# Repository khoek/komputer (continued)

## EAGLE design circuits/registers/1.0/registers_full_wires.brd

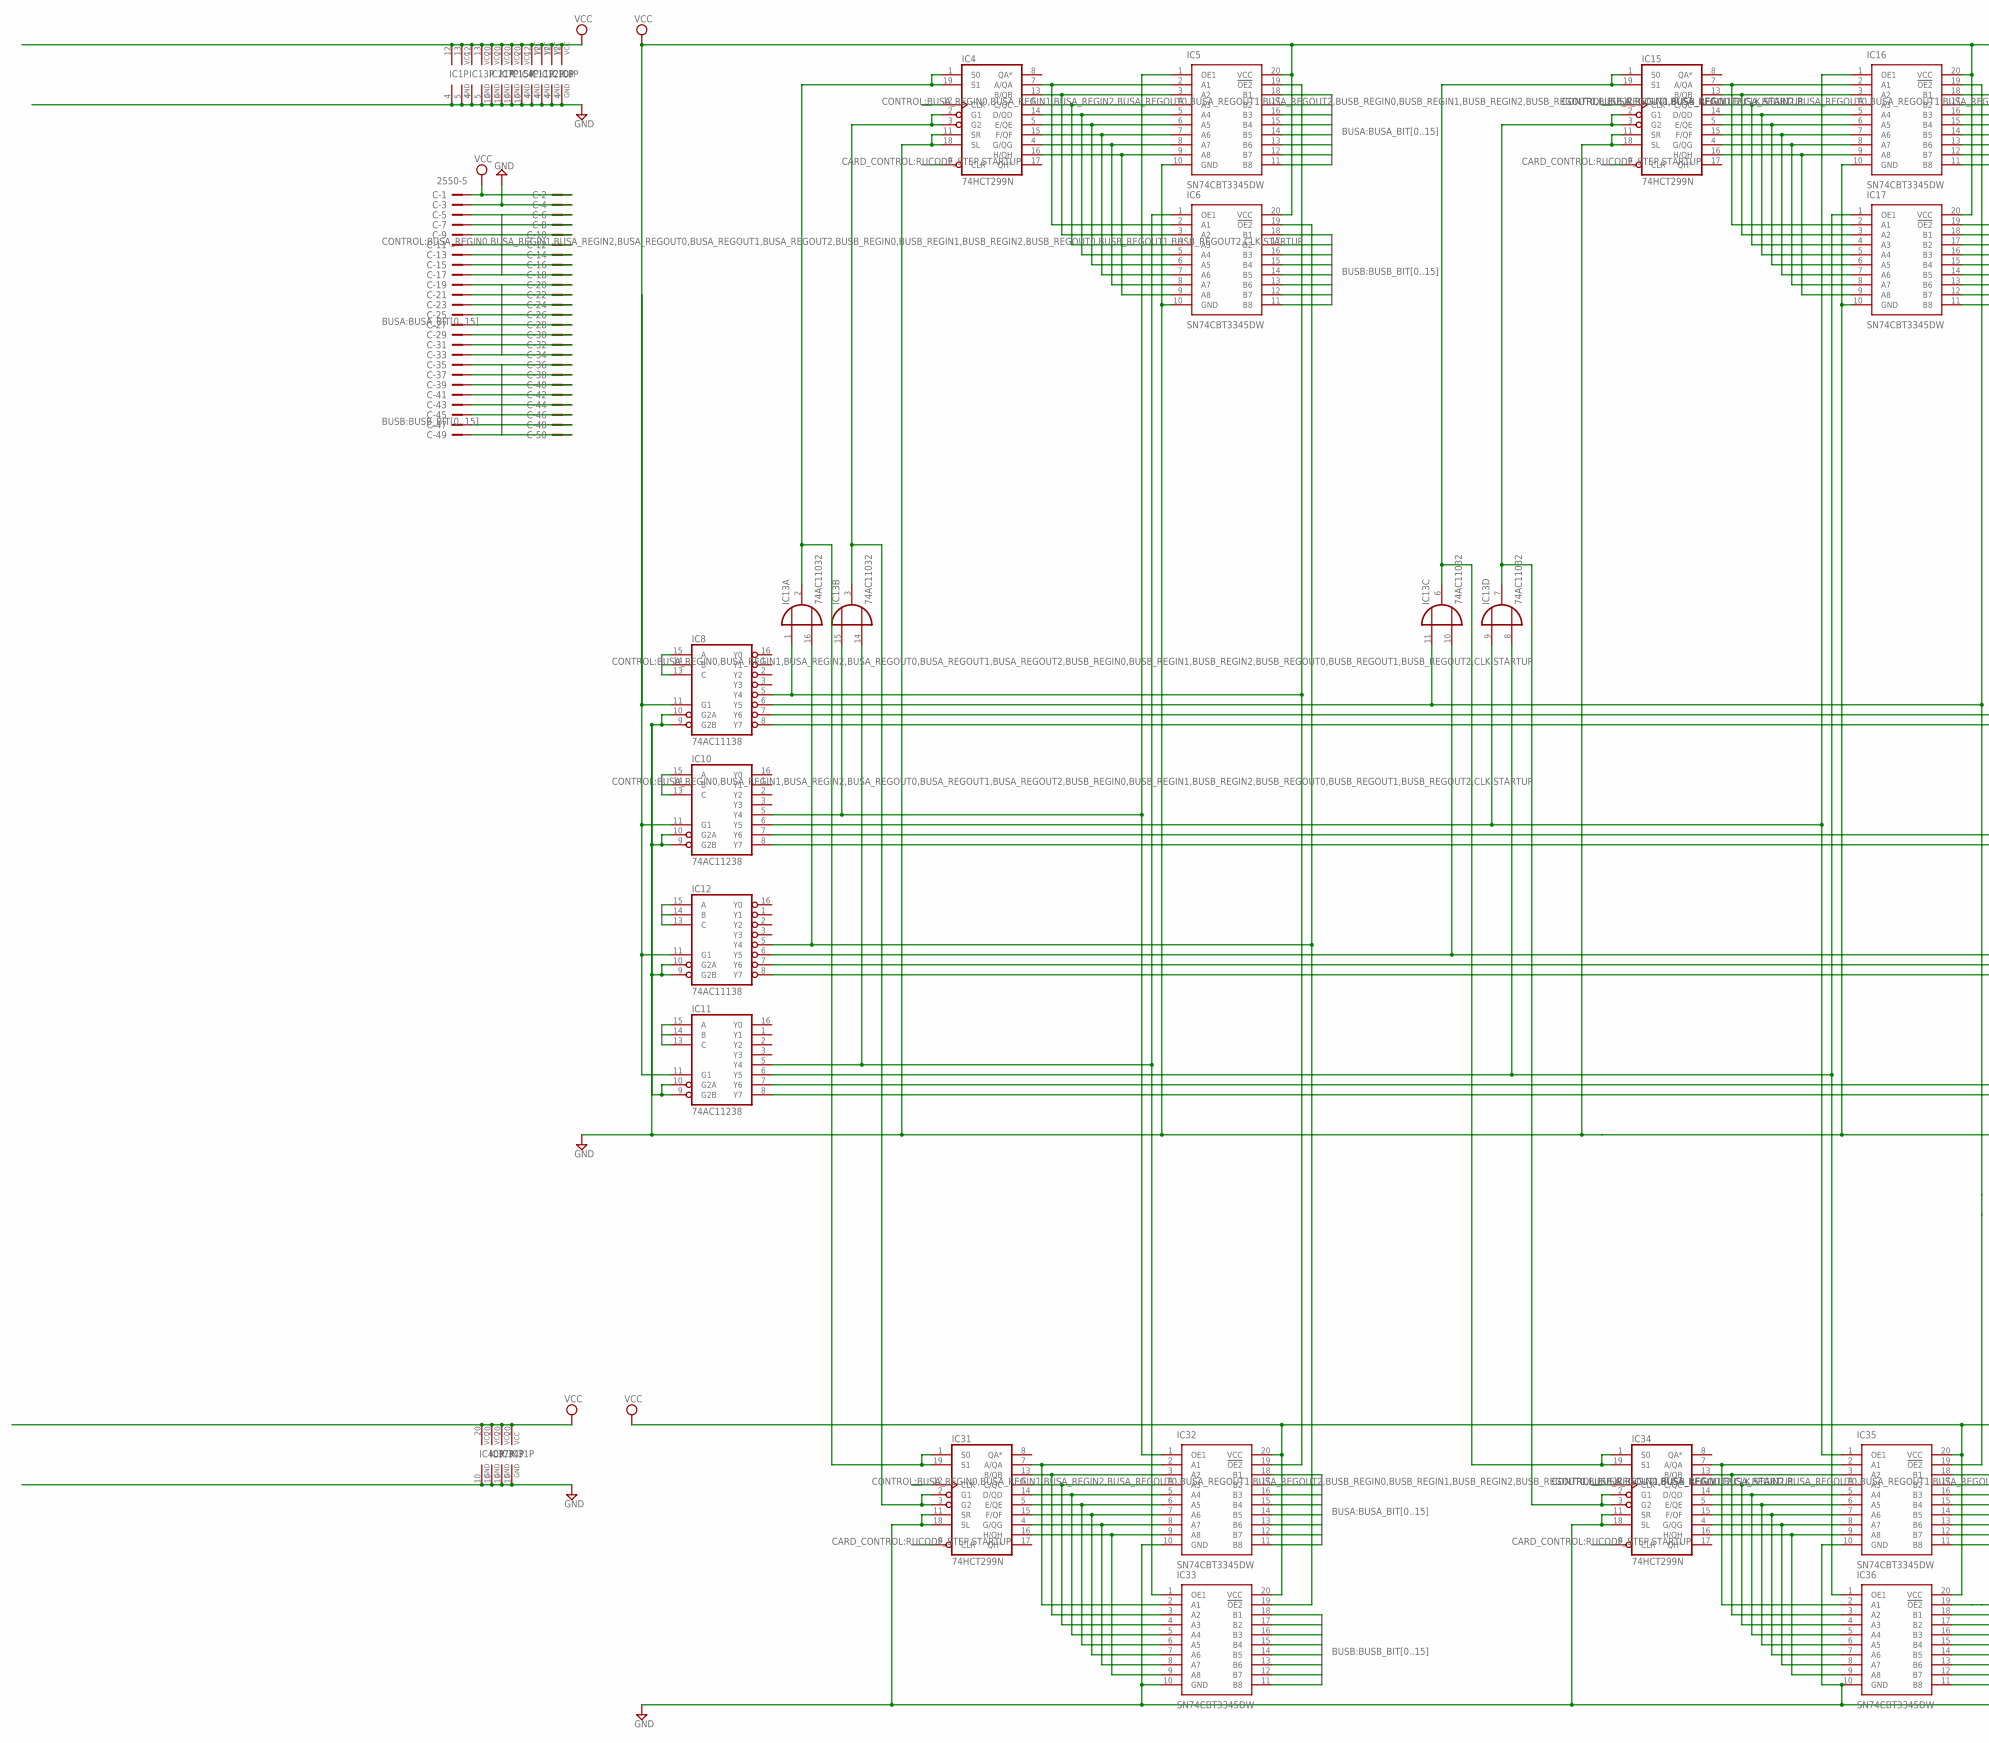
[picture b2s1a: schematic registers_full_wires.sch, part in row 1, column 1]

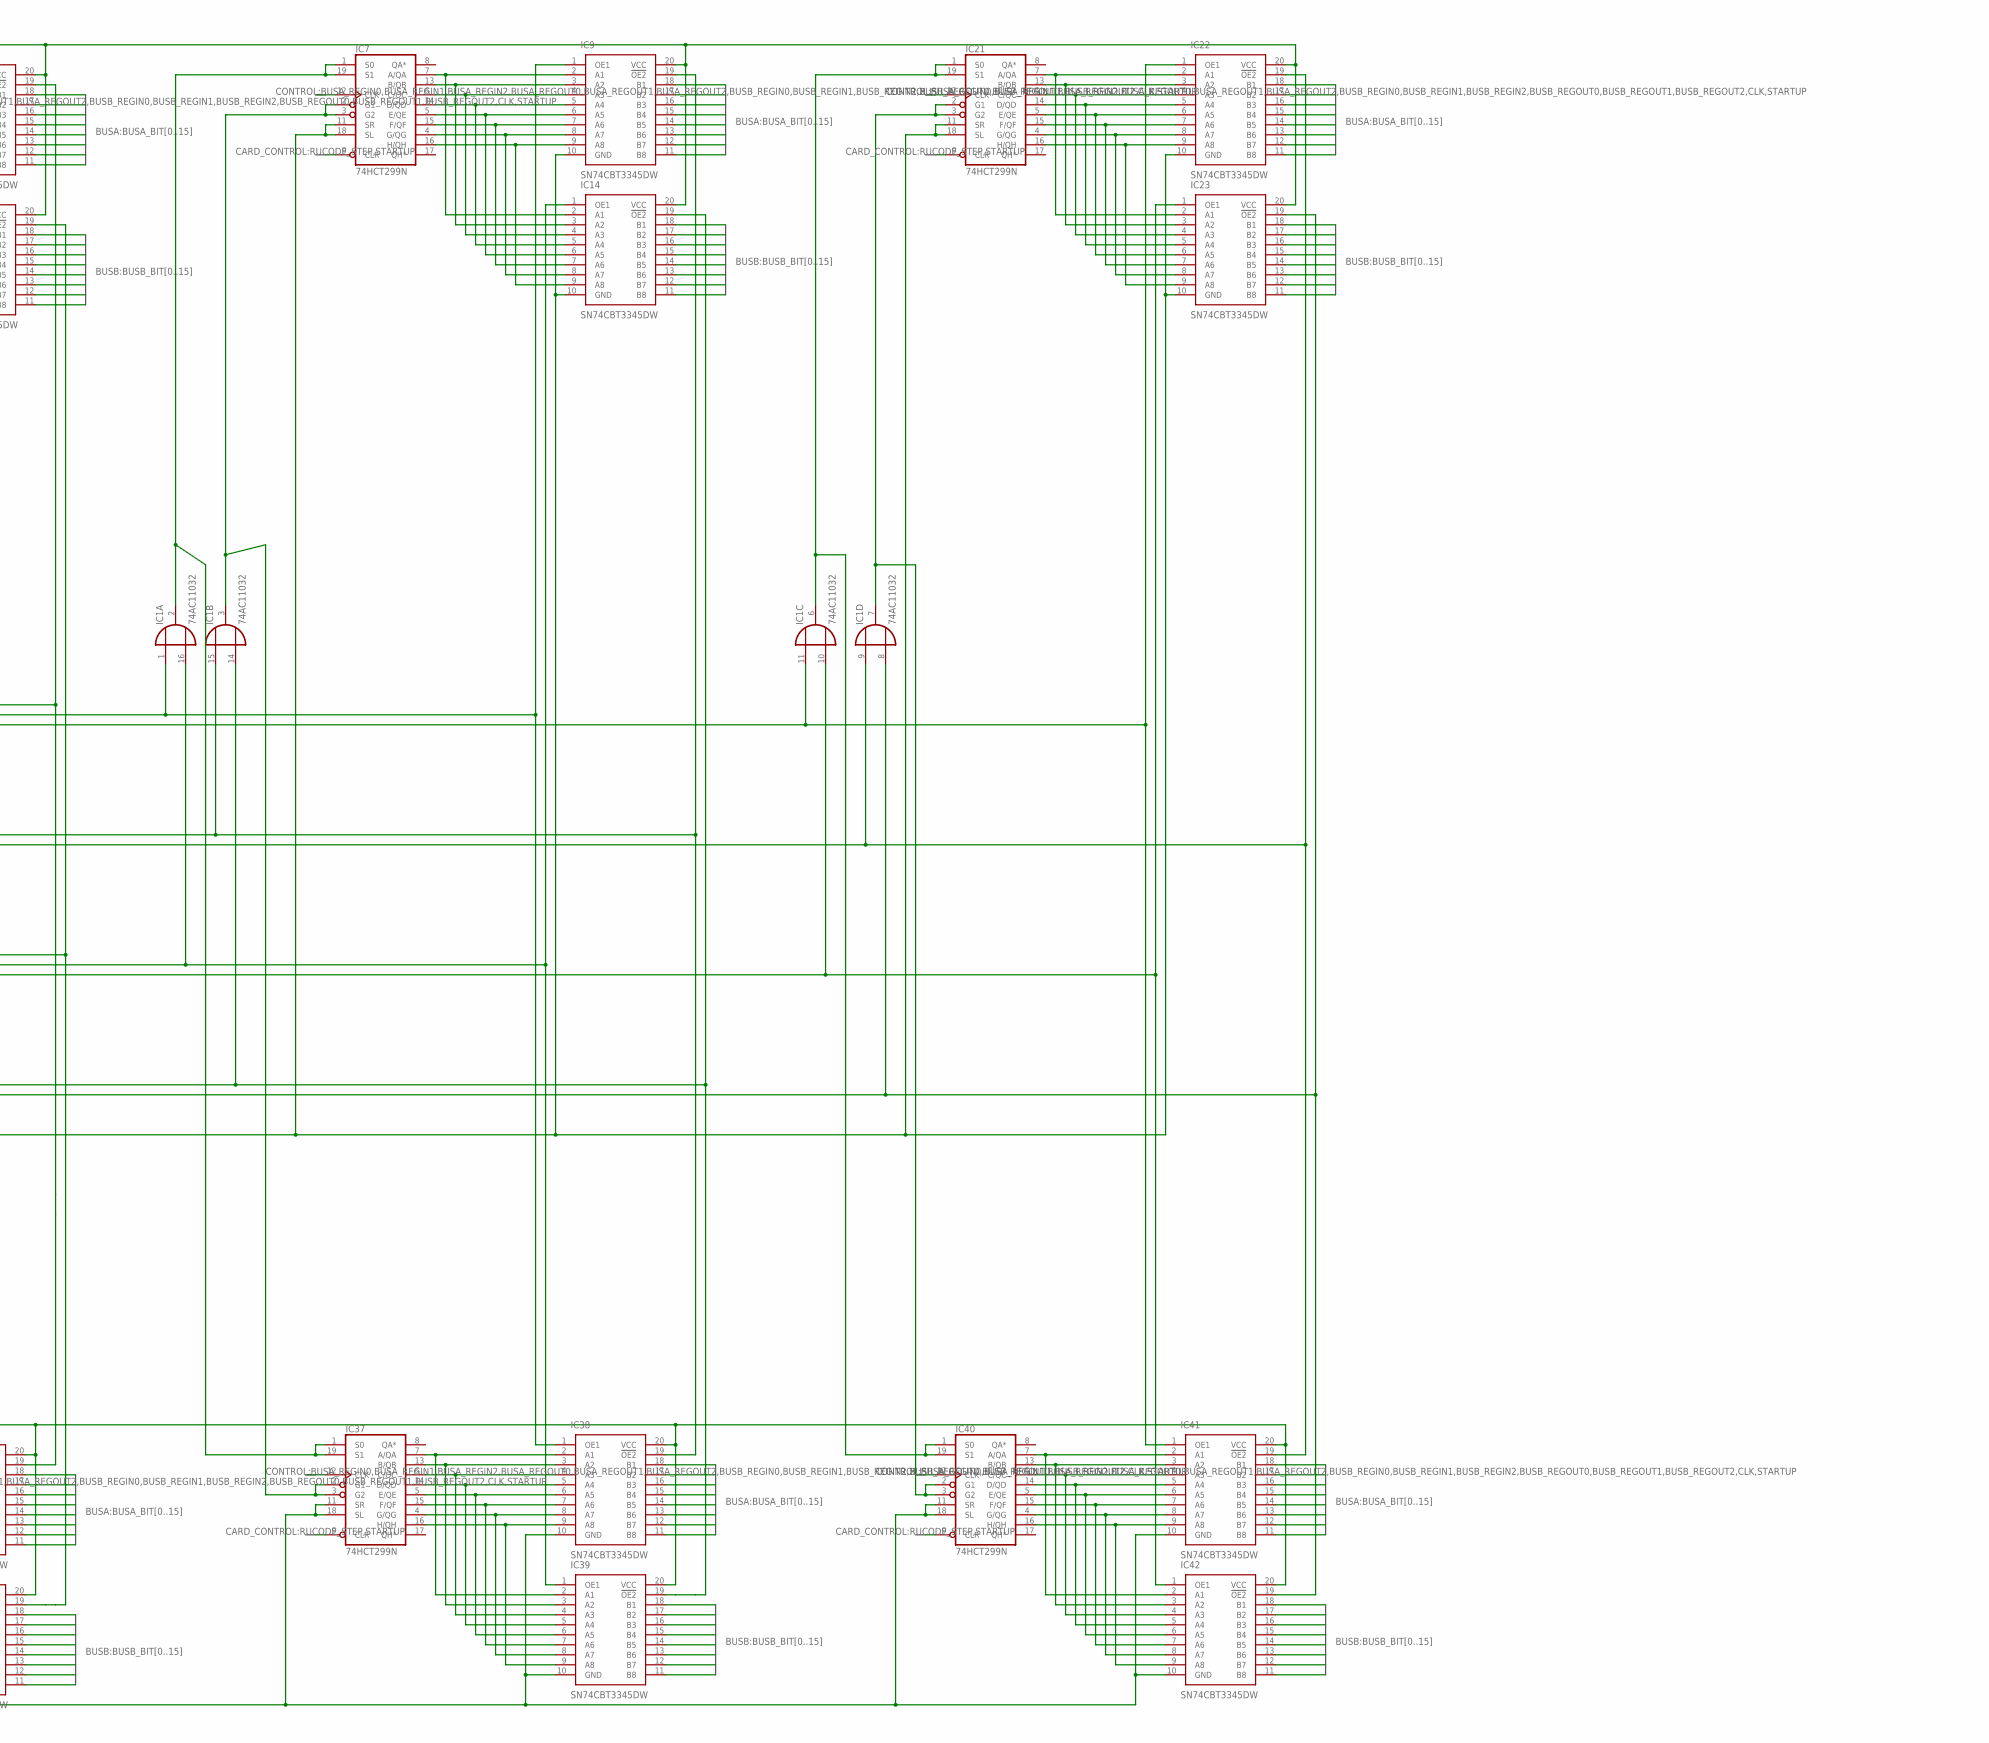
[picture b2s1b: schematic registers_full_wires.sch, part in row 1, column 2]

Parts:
C: 2550-5; PAK100/2500-5-50
IC1, IC13: 74AC11032; DIL16
IC4, IC7, IC15, IC21, IC31, IC34, IC37, IC40: 74HCT299N; DIL20
IC5, IC6, IC9, IC14, IC16, IC17, IC22, IC23, IC32, IC33, IC35, IC36, IC38, IC39, IC41, IC42: SN74CBT3345DW; SOIC127P1030X265-20N
IC8, IC12: 74AC11138; DIL16
IC10, IC11: 74AC11238; DIL16

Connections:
BUSA_BIT0: C.19, IC5.18 (B1), IC9.18 (B1), IC16.18 (B1), IC22.18 (B1)
BUSA_BIT1: C.20, IC5.17 (B2), IC9.17 (B2), IC16.17 (B2), IC22.17 (B2)
BUSA_BIT2: C.21, IC5.16 (B3), IC9.16 (B3), IC16.16 (B3), IC22.16 (B3)
BUSA_BIT3: C.22, IC5.15 (B4), IC9.15 (B4), IC16.15 (B4), IC22.15 (B4)
BUSA_BIT4: C.23, IC5.14 (B5), IC9.14 (B5), IC16.14 (B5), IC22.14 (B5)
BUSA_BIT5: C.24, IC5.13 (B6), IC9.13 (B6), IC16.13 (B6), IC22.13 (B6)
BUSA_BIT6: C.25, IC5.12 (B7), IC9.12 (B7), IC16.12 (B7), IC22.12 (B7)
BUSA_BIT7: C.26, IC5.11 (B8), IC9.11 (B8), IC16.11 (B8), IC22.11 (B8)
BUSA_BIT8: C.27, IC32.18 (B1), IC35.18 (B1), IC38.18 (B1), IC41.18 (B1)
BUSA_BIT9: C.28, IC32.17 (B2), IC35.17 (B2), IC38.17 (B2), IC41.17 (B2)
BUSA_BIT10: C.29, IC32.16 (B3), IC35.16 (B3), IC38.16 (B3), IC41.16 (B3)
BUSA_BIT11: C.30, IC32.15 (B4), IC35.15 (B4), IC38.15 (B4), IC41.15 (B4)
BUSA_BIT12: C.31, IC32.14 (B5), IC35.14 (B5), IC38.14 (B5), IC41.14 (B5)
BUSA_BIT13: C.32, IC32.13 (B6), IC35.13 (B6), IC38.13 (B6), IC41.13 (B6)
BUSA_BIT14: C.33, IC32.12 (B7), IC35.12 (B7), IC38.12 (B7), IC41.12 (B7)
BUSA_BIT15: C.34, IC32.11 (B8), IC35.11 (B8), IC38.11 (B8), IC41.11 (B8)
BUSA_REGIN0: C.7, IC8.15 (A)
BUSA_REGIN1: C.9, IC8.14 (B)
BUSA_REGIN2: C.11, IC8.13 (C)
BUSA_REGOUT0: C.13, IC10.15 (A)
BUSA_REGOUT1: C.15, IC10.14 (B)
BUSA_REGOUT2: C.17, IC10.13 (C)
BUSB_BIT0: C.35, IC6.18 (B1), IC14.18 (B1), IC17.18 (B1), IC23.18 (B1)
BUSB_BIT1: C.36, IC6.17 (B2), IC14.17 (B2), IC17.17 (B2), IC23.17 (B2)
BUSB_BIT2: C.37, IC6.16 (B3), IC14.16 (B3), IC17.16 (B3), IC23.16 (B3)
BUSB_BIT3: C.38, IC6.15 (B4), IC14.15 (B4), IC17.15 (B4), IC23.15 (B4)
BUSB_BIT4: C.39, IC6.14 (B5), IC14.14 (B5), IC17.14 (B5), IC23.14 (B5)
BUSB_BIT5: C.40, IC6.13 (B6), IC14.13 (B6), IC17.13 (B6), IC23.13 (B6)
BUSB_BIT6: C.41, IC6.12 (B7), IC14.12 (B7), IC17.12 (B7), IC23.12 (B7)
BUSB_BIT7: C.42, IC6.11 (B8), IC14.11 (B8), IC17.11 (B8), IC23.11 (B8)
BUSB_BIT8: C.43, IC33.18 (B1), IC36.18 (B1), IC39.18 (B1), IC42.18 (B1)
BUSB_BIT9: C.44, IC33.17 (B2), IC36.17 (B2), IC39.17 (B2), IC42.17 (B2)
BUSB_BIT10: C.45, IC33.16 (B3), IC36.16 (B3), IC39.16 (B3), IC42.16 (B3)
BUSB_BIT11: C.46, IC33.15 (B4), IC36.15 (B4), IC39.15 (B4), IC42.15 (B4)
BUSB_BIT12: C.47, IC33.14 (B5), IC36.14 (B5), IC39.14 (B5), IC42.14 (B5)
BUSB_BIT13: C.48, IC33.13 (B6), IC36.13 (B6), IC39.13 (B6), IC42.13 (B6)
BUSB_BIT14: C.49, IC33.12 (B7), IC36.12 (B7), IC39.12 (B7), IC42.12 (B7)
BUSB_BIT15: C.50, IC33.11 (B8), IC36.11 (B8), IC39.11 (B8), IC42.11 (B8)
BUSB_REGIN0: C.8, IC12.15 (A)
BUSB_REGIN1: C.10, IC12.14 (B)
BUSB_REGIN2: C.12, IC12.13 (C)
BUSB_REGOUT0: C.14, IC11.15 (A)
BUSB_REGOUT1: C.16, IC11.14 (B)
BUSB_REGOUT2: C.18, IC11.13 (C)
CLK: C.5, IC4.12 (CLK), IC7.12 (CLK), IC15.12 (CLK), IC21.12 (CLK), IC31.12 (CLK), IC34.12 (CLK), IC37.12 (CLK), IC40.12 (CLK)
GND: C.3, C.4, IC1.4 (GND), IC1.5 (GND), IC4.10 (GND), IC4.11 (SR), IC4.18 (SL), IC5.10 (GND), IC6.10 (GND), IC7.10 (GND), IC7.11 (SR), IC7.18 (SL), IC8.4 (GND), IC8.9 (G2B), IC8.10 (G2A), IC9.10 (GND), IC10.4 (GND), IC10.9 (G2B), IC10.10 (G2A), IC11.4 (GND), IC11.9 (G2B), IC11.10 (G2A), IC12.4 (GND), IC12.9 (G2B), IC12.10 (G2A), IC13.4 (GND), IC13.5 (GND), IC14.10 (GND), IC15.10 (GND), IC15.11 (SR), IC15.18 (SL), IC16.10 (GND), IC17.10 (GND), IC21.10 (GND), IC21.11 (SR), IC21.18 (SL), IC22.10 (GND), IC23.10 (GND), IC31.10 (GND), IC31.11 (SR), IC31.18 (SL), IC32.10 (GND), IC33.10 (GND), IC34.10 (GND), IC34.11 (SR), IC34.18 (SL), IC35.10 (GND), IC36.10 (GND), IC37.10 (GND), IC37.11 (SR), IC37.18 (SL), IC38.10 (GND), IC39.10 (GND), IC40.10 (GND), IC40.11 (SR), IC40.18 (SL), IC41.10 (GND), IC42.10 (GND)
unnamed: IC34.16 (H/QH), IC35.9 (A8), IC36.9 (A8)
unnamed: IC1.8 (I2), IC11.8 (Y7), IC23.19 (!OE2), IC42.19 (!OE2)
unnamed: IC4.7 (A/QA), IC5.2 (A1), IC6.2 (A1)
unnamed: IC4.13 (B/QB), IC5.3 (A2), IC6.3 (A2)
unnamed: IC4.6 (C/QC), IC5.4 (A3), IC6.4 (A3)
unnamed: IC4.14 (D/QD), IC5.5 (A4), IC6.5 (A4)
unnamed: IC4.5 (E/QE), IC5.6 (A5), IC6.6 (A5)
unnamed: IC4.15 (F/QF), IC5.7 (A6), IC6.7 (A6)
unnamed: IC4.4 (G/QG), IC5.8 (A7), IC6.8 (A7)
unnamed: IC4.16 (H/QH), IC5.9 (A8), IC6.9 (A8)
unnamed: IC7.7 (A/QA), IC9.2 (A1), IC14.2 (A1)
unnamed: IC7.13 (B/QB), IC9.3 (A2), IC14.3 (A2)
unnamed: IC7.6 (C/QC), IC9.4 (A3), IC14.4 (A3)
unnamed: IC7.14 (D/QD), IC9.5 (A4), IC14.5 (A4)
unnamed: IC7.5 (E/QE), IC9.6 (A5), IC14.6 (A5)
unnamed: IC5.1 (OE1), IC10.5 (Y4), IC13.15 (I1), IC32.1 (OE1)
unnamed: IC7.15 (F/QF), IC9.7 (A6), IC14.7 (A6)
unnamed: IC7.4 (G/QG), IC9.8 (A7), IC14.8 (A7)
unnamed: IC7.16 (H/QH), IC9.9 (A8), IC14.9 (A8)
unnamed: IC15.7 (A/QA), IC16.2 (A1), IC17.2 (A1)
unnamed: IC15.13 (B/QB), IC16.3 (A2), IC17.3 (A2)
unnamed: IC15.6 (C/QC), IC16.4 (A3), IC17.4 (A3)
unnamed: IC15.14 (D/QD), IC16.5 (A4), IC17.5 (A4)
unnamed: IC15.5 (E/QE), IC16.6 (A5), IC17.6 (A5)
unnamed: IC15.15 (F/QF), IC16.7 (A6), IC17.7 (A6)
unnamed: IC15.4 (G/QG), IC16.8 (A7), IC17.8 (A7)
unnamed: IC15.16 (H/QH), IC16.9 (A8), IC17.9 (A8)
unnamed: IC21.7 (A/QA), IC22.2 (A1), IC23.2 (A1)
unnamed: IC21.13 (B/QB), IC22.3 (A2), IC23.3 (A2)
unnamed: IC21.6 (C/QC), IC22.4 (A3), IC23.4 (A3)
unnamed: IC21.14 (D/QD), IC22.5 (A4), IC23.5 (A4)
unnamed: IC21.5 (E/QE), IC22.6 (A5), IC23.6 (A5)
unnamed: IC21.15 (F/QF), IC22.7 (A6), IC23.7 (A6)
unnamed: IC21.4 (G/QG), IC22.8 (A7), IC23.8 (A7)
unnamed: IC21.16 (H/QH), IC22.9 (A8), IC23.9 (A8)
unnamed: IC5.19 (!OE2), IC8.5 (Y4), IC13.1 (I1), IC32.19 (!OE2)
unnamed: IC31.7 (A/QA), IC32.2 (A1), IC33.2 (A1)
unnamed: IC31.13 (B/QB), IC32.3 (A2), IC33.3 (A2)
unnamed: IC6.19 (!OE2), IC12.5 (Y4), IC13.16 (I2), IC33.19 (!OE2)
unnamed: IC31.6 (C/QC), IC32.4 (A3), IC33.4 (A3)
unnamed: IC31.14 (D/QD), IC32.5 (A4), IC33.5 (A4)
unnamed: IC4.2 (G1), IC4.3 (G2), IC13.3 (O), IC31.2 (G1), IC31.3 (G2)
unnamed: IC4.1 (S0), IC4.19 (S1), IC13.2 (O), IC31.1 (S0), IC31.19 (S1)
unnamed: IC31.5 (E/QE), IC32.6 (A5), IC33.6 (A5)
unnamed: IC31.15 (F/QF), IC32.7 (A6), IC33.7 (A6)
unnamed: IC31.4 (G/QG), IC32.8 (A7), IC33.8 (A7)
unnamed: IC31.16 (H/QH), IC32.9 (A8), IC33.9 (A8)
unnamed: IC34.7 (A/QA), IC35.2 (A1), IC36.2 (A1)
unnamed: IC34.13 (B/QB), IC35.3 (A2), IC36.3 (A2)
unnamed: IC34.6 (C/QC), IC35.4 (A3), IC36.4 (A3)
unnamed: IC34.14 (D/QD), IC35.5 (A4), IC36.5 (A4)
unnamed: IC13.7 (O), IC15.2 (G1), IC15.3 (G2), IC34.2 (G1), IC34.3 (G2)
unnamed: IC13.6 (O), IC15.1 (S0), IC15.19 (S1), IC34.1 (S0), IC34.19 (S1)
unnamed: IC34.5 (E/QE), IC35.6 (A5), IC36.6 (A5)
unnamed: IC34.15 (F/QF), IC35.7 (A6), IC36.7 (A6)
unnamed: IC34.4 (G/QG), IC35.8 (A7), IC36.8 (A7)
unnamed: IC37.7 (A/QA), IC38.2 (A1), IC39.2 (A1)
unnamed: IC37.13 (B/QB), IC38.3 (A2), IC39.3 (A2)
unnamed: IC37.6 (C/QC), IC38.4 (A3), IC39.4 (A3)
unnamed: IC37.14 (D/QD), IC38.5 (A4), IC39.5 (A4)
unnamed: IC1.3 (O), IC7.2 (G1), IC7.3 (G2), IC37.2 (G1), IC37.3 (G2)
unnamed: IC1.2 (O), IC7.1 (S0), IC7.19 (S1), IC37.1 (S0), IC37.19 (S1)
unnamed: IC37.5 (E/QE), IC38.6 (A5), IC39.6 (A5)
unnamed: IC37.15 (F/QF), IC38.7 (A6), IC39.7 (A6)
unnamed: IC37.4 (G/QG), IC38.8 (A7), IC39.8 (A7)
unnamed: IC37.16 (H/QH), IC38.9 (A8), IC39.9 (A8)
unnamed: IC40.7 (A/QA), IC41.2 (A1), IC42.2 (A1)
unnamed: IC40.13 (B/QB), IC41.3 (A2), IC42.3 (A2)
unnamed: IC40.6 (C/QC), IC41.4 (A3), IC42.4 (A3)
unnamed: IC40.14 (D/QD), IC41.5 (A4), IC42.5 (A4)
unnamed: IC1.7 (O), IC21.2 (G1), IC21.3 (G2), IC40.2 (G1), IC40.3 (G2)
unnamed: IC1.6 (O), IC21.1 (S0), IC21.19 (S1), IC40.1 (S0), IC40.19 (S1)
unnamed: IC40.5 (E/QE), IC41.6 (A5), IC42.6 (A5)
unnamed: IC40.15 (F/QF), IC41.7 (A6), IC42.7 (A6)
unnamed: IC40.4 (G/QG), IC41.8 (A7), IC42.8 (A7)
unnamed: IC40.16 (H/QH), IC41.9 (A8), IC42.9 (A8)
unnamed: IC6.1 (OE1), IC11.5 (Y4), IC13.14 (I2), IC33.1 (OE1)
unnamed: IC8.6 (Y5), IC13.11 (I1), IC16.19 (!OE2), IC35.19 (!OE2)
unnamed: IC12.6 (Y5), IC13.10 (I2), IC17.19 (!OE2), IC36.19 (!OE2)
unnamed: IC10.6 (Y5), IC13.9 (I1), IC16.1 (OE1), IC35.1 (OE1)
unnamed: IC11.6 (Y5), IC13.8 (I2), IC17.1 (OE1), IC36.1 (OE1)
unnamed: IC1.1 (I1), IC8.7 (Y6), IC9.1 (OE1), IC38.1 (OE1)
unnamed: IC1.16 (I2), IC12.7 (Y6), IC14.1 (OE1), IC39.1 (OE1)
unnamed: IC1.15 (I1), IC9.19 (!OE2), IC10.7 (Y6), IC38.19 (!OE2)
unnamed: IC1.14 (I2), IC11.7 (Y6), IC14.19 (!OE2), IC39.19 (!OE2)
unnamed: IC1.9 (I1), IC10.8 (Y7), IC22.19 (!OE2), IC41.19 (!OE2)
unnamed: IC1.10 (I2), IC12.8 (Y7), IC23.1 (OE1), IC42.1 (OE1)
unnamed: IC1.11 (I1), IC8.8 (Y7), IC22.1 (OE1), IC41.1 (OE1)
STARTUP: C.6, IC4.9 (CLR), IC7.9 (CLR), IC15.9 (CLR), IC21.9 (CLR), IC31.9 (CLR), IC34.9 (CLR), IC37.9 (CLR), IC40.9 (CLR)
VCC: C.1, C.2, IC1.12 (VCC), IC1.13 (VCC), IC4.20 (VCC), IC5.20 (VCC), IC6.20 (VCC), IC7.20 (VCC), IC8.11 (G1), IC8.12 (VCC), IC9.20 (VCC), IC10.11 (G1), IC10.12 (VCC), IC11.11 (G1), IC11.12 (VCC), IC12.11 (G1), IC12.12 (VCC), IC13.12 (VCC), IC13.13 (VCC), IC14.20 (VCC), IC15.20 (VCC), IC16.20 (VCC), IC17.20 (VCC), IC21.20 (VCC), IC22.20 (VCC), IC23.20 (VCC), IC31.20 (VCC), IC32.20 (VCC), IC33.20 (VCC), IC34.20 (VCC), IC35.20 (VCC), IC36.20 (VCC), IC37.20 (VCC), IC38.20 (VCC), IC39.20 (VCC), IC40.20 (VCC), IC41.20 (VCC), IC42.20 (VCC)

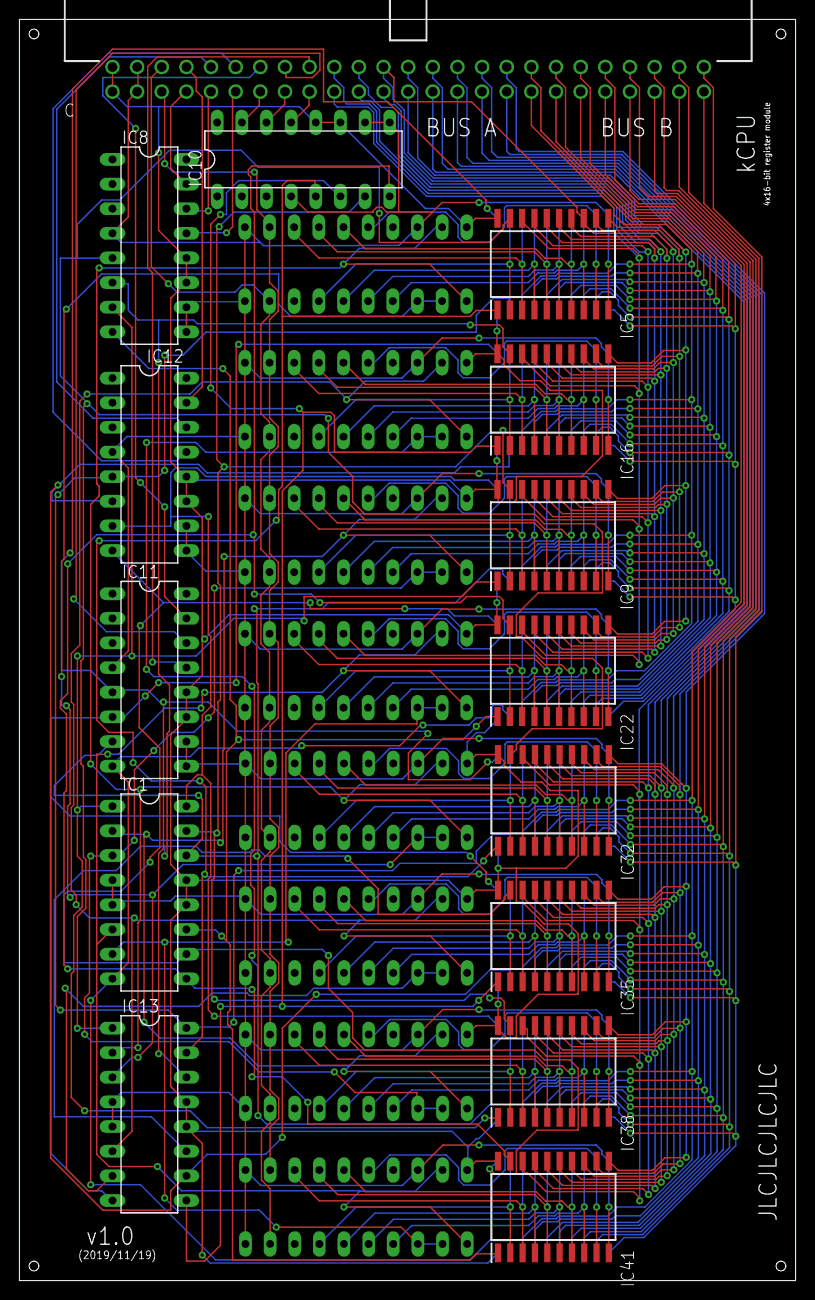
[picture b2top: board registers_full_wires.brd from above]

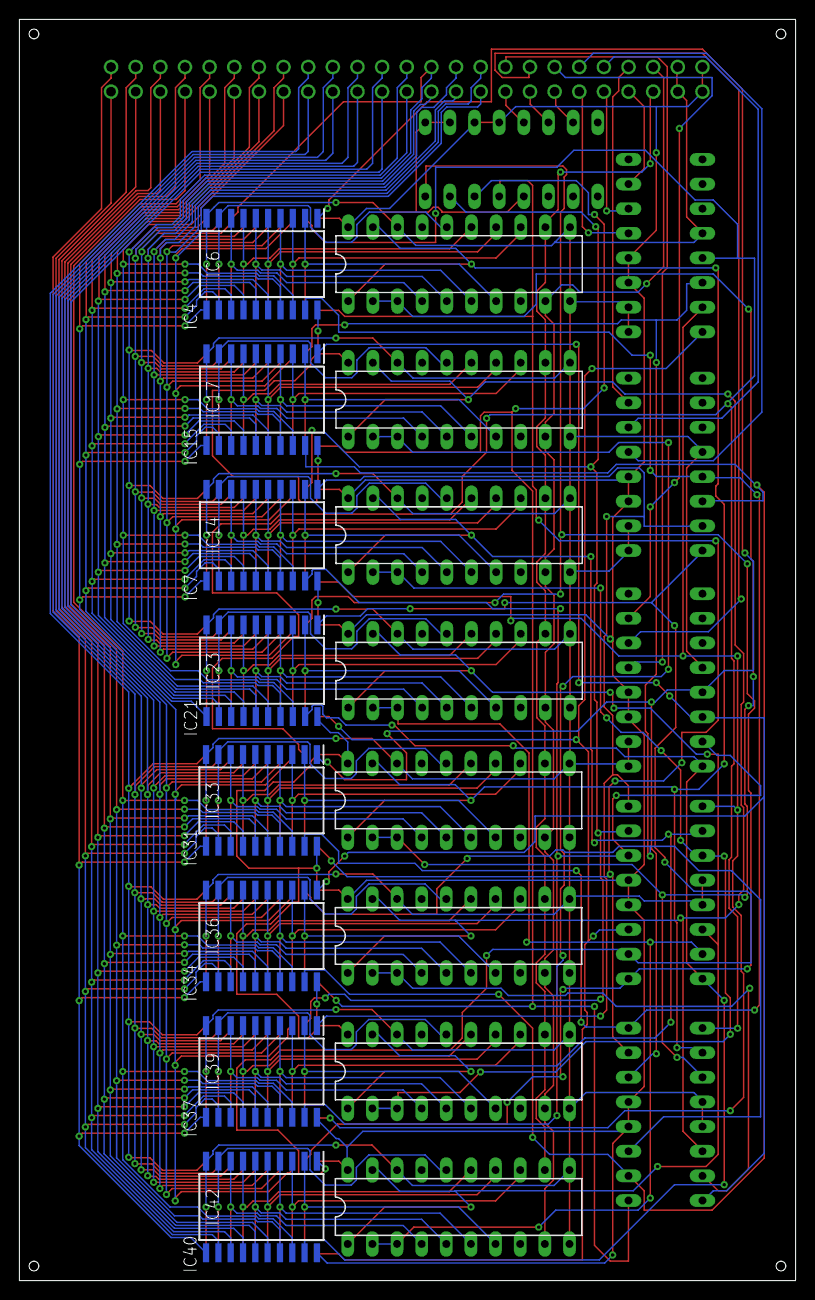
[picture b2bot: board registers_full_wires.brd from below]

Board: 2 copper layers, 80.0 x 130.0 mm, 31 parts (16 on the bottom side), 136 nets.
